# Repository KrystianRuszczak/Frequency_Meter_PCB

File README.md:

# STM32 Frequency Meter PCB

A four-layer KiCad board for measuring the frequency of periodic signals in the **50–100 MHz** range. A 50 Ω SMA input feeds an analog filter and amplifier. The STM32 counts pulses from that front end and is intended to show the result on a small OLED display.

| Design target | Value |
|---|---|
| Input frequency | 50–100 MHz |
| Minimum input amplitude | 10 mV peak (20 mV peak-to-peak for a sine wave) |
| Counter input after division | 25–50 MHz |
| Timebase | 16 MHz crystal |
| Power and data | 5 V from USB-C; USB 2.0 Full-Speed data lines routed to the STM32 |
| Display | 1.3-inch, 128 × 64 I²C OLED |

## Signal path

1. The signal enters through a 50 Ω edge-mount SMA connector and passes through a Butterworth LC band-pass filter designed for 50–100 MHz. A 49.9 Ω resistor terminates the filter output.
2. The LMH6629 amplifies the filtered signal. The REF2033 supplies a 1.65 V bias for the amplifier and comparison threshold.
3. The TLV3601 converts the amplified waveform into digital pulses. The SN74LVC1G80 divides the pulse rate by two before it reaches the STM32 on PA1.
4. The firmware is intended to count rising edges in a timed gate and calculate the input frequency as `f_in = 2 × counted_edges / gate_time`. With a 75 MHz input, the expected rate at PA1 is 37.5 MHz.

The board includes BOOT0 and RESET buttons, SWD access pads and test points for the comparator output, divided clock, reference and power rails.

## Key components

| Reference | Part | Role |
|---|---|---|
| IC1 | LMH6629MF/NOPB | RF amplifier |
| IC2 | SN74LVC1G80DBVR | Divide-by-two stage |
| IC3 | REF2033AIDDCT | 1.65 V bias output |
| IC4 | TLV3601DBVR | High-speed comparator |
| IC5 | USBLC6-4SC6 | USB data-line ESD protection |
| IC6 | STM32G431KBT6 | Timer-based pulse counting, USB and display control |
| U2 | AP2112K-3.3 | 3.3 V regulator |
| Y1 | ABM3B-16.000MHZ-10-1-U-T | External 16 MHz crystal |
| J1 | 50 Ω edge-mount SMA | RF input; PCB footprint based on Amphenol 132289 |
| J2 | USB4105-GF-A | USB-C power and data |
| DS1 | 1.3-inch, 128 × 64 I²C OLED | Display; header order: GND, 3.3 V, SCL, SDA |

The current PCB uses the **USBLC6-4SC6**. The board traces join pads 3 and 4 for D+ and pads 1 and 6 for D−; the four-channel protection device does not bridge those pairs internally.

## KiCad files

- [Project](pcb_design/Frequency_Meter.kicad_pro)
- [Schematic](pcb_design/Frequency_Meter.kicad_sch)
- [Four-layer PCB](pcb_design/Frequency_Meter.kicad_pcb)

Open the project in KiCad and use the schematic for passive component values and reference designators. Full library editing requires the local symbol and footprint libraries and their project library tables. Those files, along with the simulation workspaces and custom design rules, are excluded by the current `.gitignore`. If working from a clean clone, obtain the missing files separately and place the libraries where the tables expect them.

## Validation status

The schematic and four-layer layout are available. Transient simulations at **75 MHz and 10 mV peak** checked whether the front end still produced the expected pulse train in the presence of out-of-band interference. At **20 mV peak**, the tested interferers at **18, 21, 23 and 207 MHz** did not visibly add or remove pulses in the plotted windows. A stronger **207 MHz** interferer at **355 mV peak** produced extra transitions. These are simulation results for specific test cases, not a hardware interference limit.

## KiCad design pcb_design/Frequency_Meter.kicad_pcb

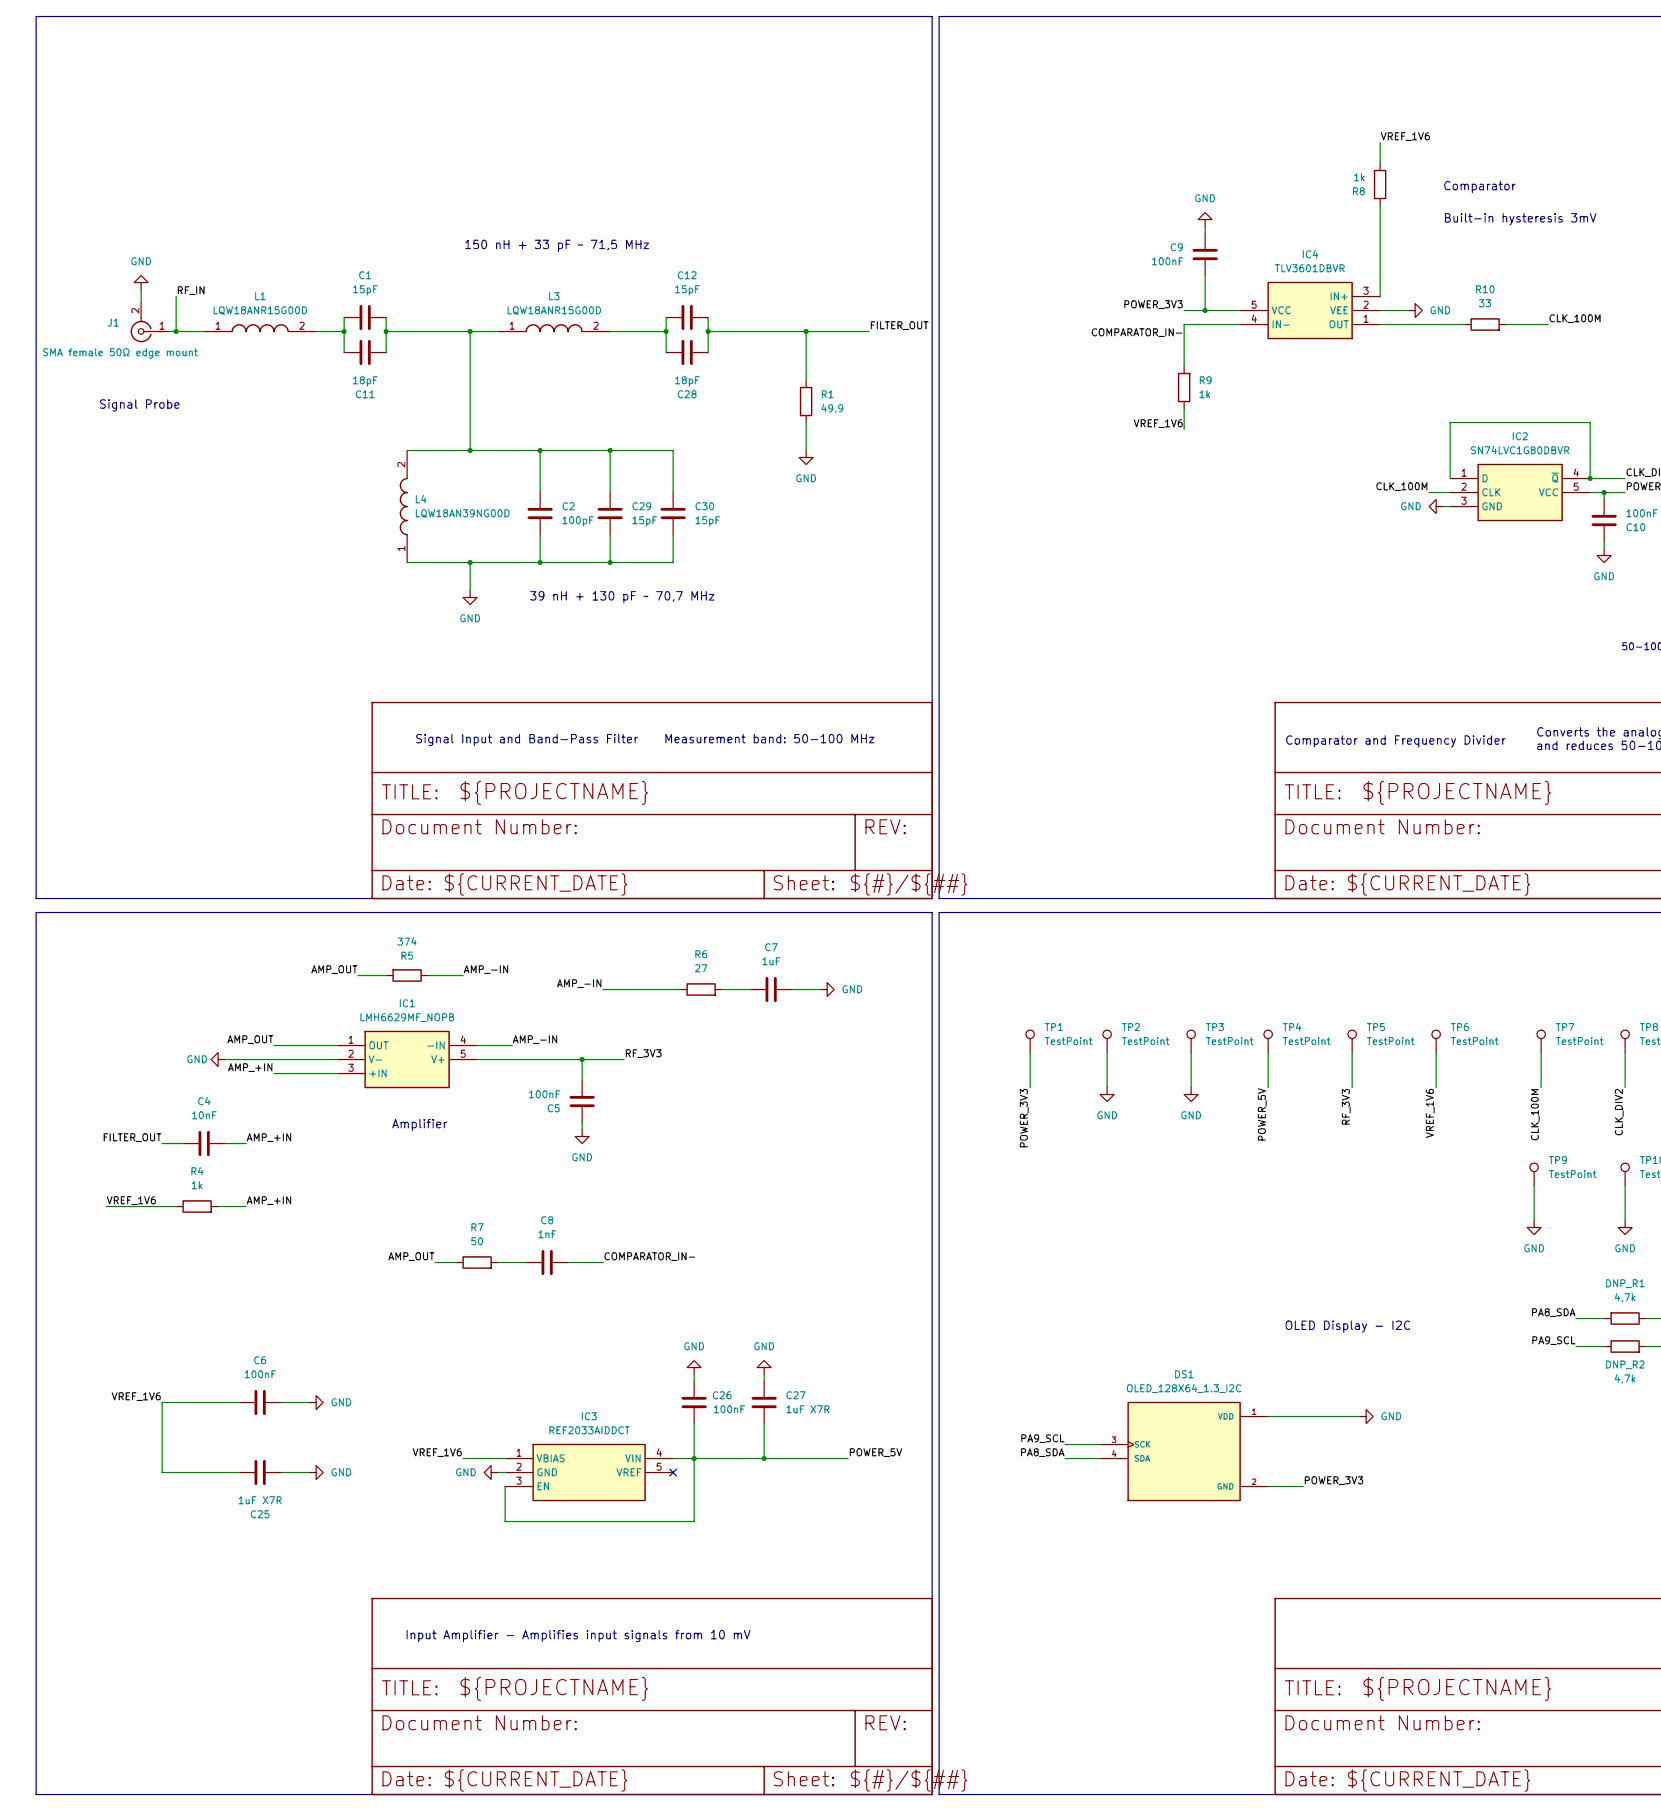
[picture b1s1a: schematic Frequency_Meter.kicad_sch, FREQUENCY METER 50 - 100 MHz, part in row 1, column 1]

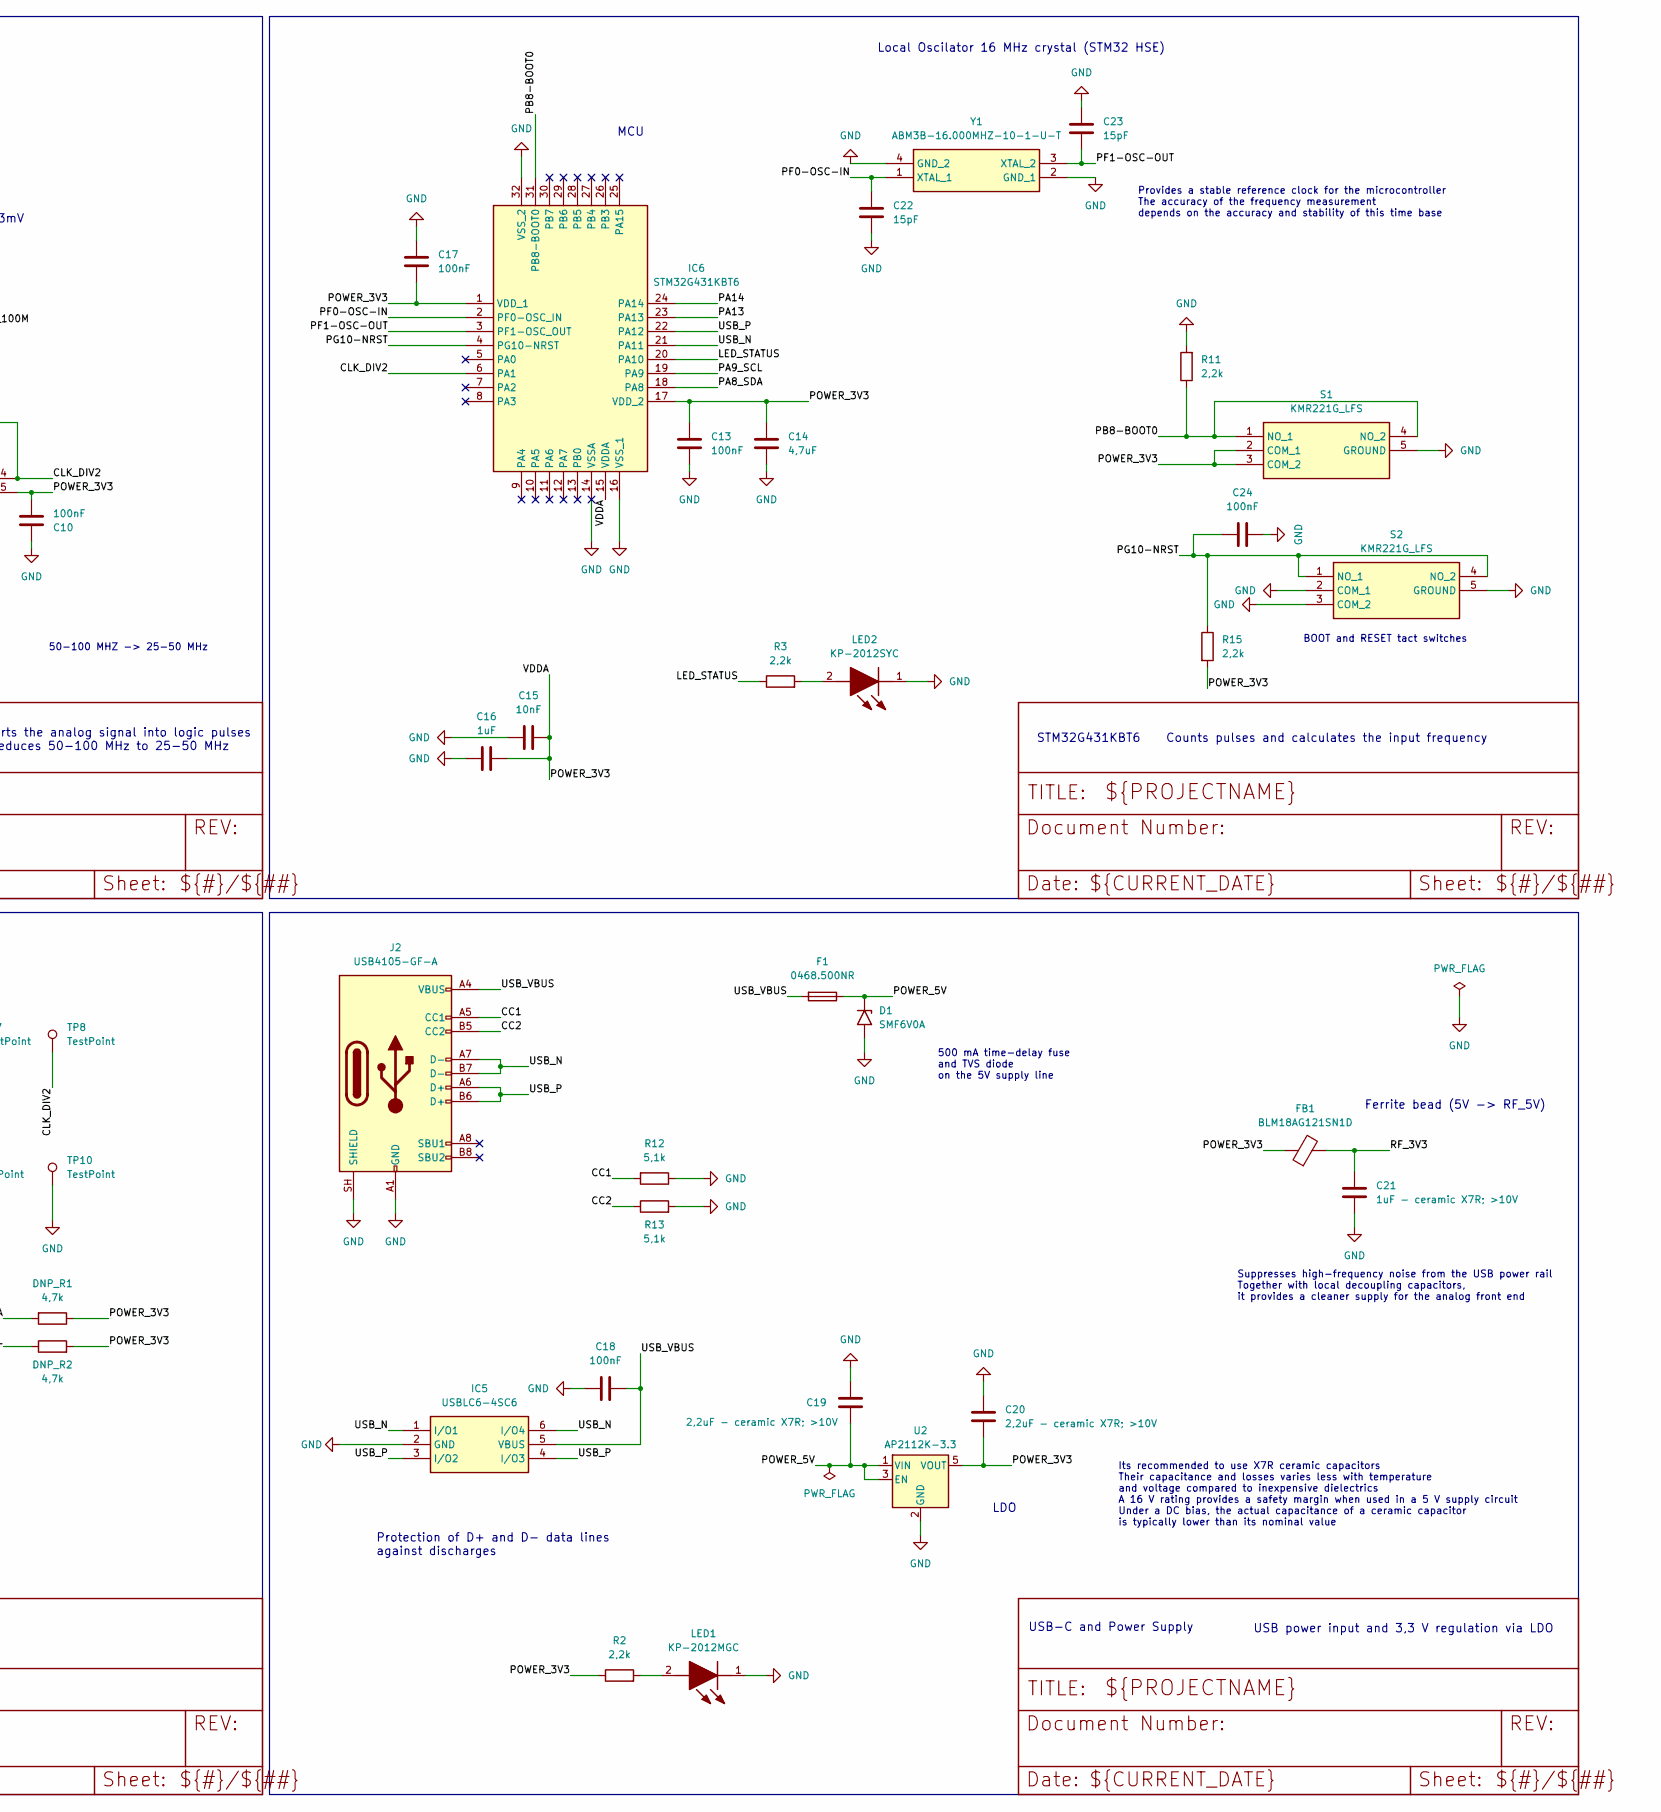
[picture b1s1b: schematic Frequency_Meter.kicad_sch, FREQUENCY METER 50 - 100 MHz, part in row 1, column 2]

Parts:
C1, C12, C22, C23, C29, C30: 15pF; C_0603_1608Metric_Pad1.08x0.95mm_HandSolder
C2: 100pF; C_0603_1608Metric_Pad1.08x0.95mm_HandSolder
C4, C15: 10nF; C_0805_2012Metric
C5, C6, C9, C10, C13, C17, C18, C24, C26: 100nF; C_0603_1608Metric_Pad1.08x0.95mm_HandSolder
C7, C16: 1uF; C_0805_2012Metric
C8: 1nF; C_0603_1608Metric_Pad1.08x0.95mm_HandSolder
C11, C28: 18pF; C_0603_1608Metric_Pad1.08x0.95mm_HandSolder
C14: 4,7uF; C_0805_2012Metric
C19, C20: 2,2uF - ceramic X7R; >10V; C_0805_2012Metric
C21: 1uF - ceramic X7R; >10V; C_0805_2012Metric
C25, C27: 1uF X7R; C_0805_2012Metric
D1: SMF6V0A; D_SMF
DNP_R1, DNP_R2: 4,7k; R_0603_1608Metric_Pad0.98x0.95mm_HandSolder
DS1: OLED_128X64_1.3_I2C; LCD_OLED_128X64_1.3_I2C; PARTREV NA
F1: 0468.500NR; Fuse_1206_3216Metric
FB1: BLM18AG121SN1D; L_0603_1608Metric_Pad1.05x0.95mm_HandSolder
IC1: LMH6629MF_NOPB; SOT95P280X145-5N; Mouser Part Number 926-LMH6629MF/NOPB
IC2: SN74LVC1G80DBVR; SOT95P280X145-5N; Mouser Part Number 595-SN74LVC1G80DBVR
IC3: REF2033AIDDCT; SOT95P280X110-5N; Mouser Part Number 595-REF2033AIDDCT
IC4: TLV3601DBVR; SOT95P280X145-5N; Mouser Part Number 595-TLV3601DBVR
IC5: USBLC6-4SC6; SOT95P280X145-6N; Manufacturer_Part_Number USBLC6-4SC6
IC6: STM32G431KBT6; QFP80P900X900X160-32N; Manufacturer_Part_Number STM32G431KBT6
J1: SMA female 50Ω edge mount; SMA_Amphenol_132289_EdgeMount
J2: USB4105-GF-A; USB_C_Receptacle_GCT_USB4105-xx-A_16P_TopMnt_Horizontal
L1, L3: LQW18ANR15G00D; L_0603_1608Metric_Pad1.05x0.95mm_HandSolder; Manufacturer_Part_Number LQW18ANR15G00D
L4: LQW18AN39NG00D; L_0603_1608Metric_Pad1.05x0.95mm_HandSolder; Manufacturer_Part_Number LQW18AN39NG00D
LED1: KP-2012MGC; LEDC2012X110N; Manufacturer_Part_Number KP-2012MGC
LED2: KP-2012SYC; LEDC2012X110N; Manufacturer_Part_Number KP-2012SYC
R1: 49,9; R_0603_1608Metric_Pad0.98x0.95mm_HandSolder
R2, R3, R11, R15: 2,2k; R_0603_1608Metric_Pad0.98x0.95mm_HandSolder
R4, R8, R9: 1k; R_0603_1608Metric_Pad0.98x0.95mm_HandSolder
R5: 374; R_0603_1608Metric_Pad0.98x0.95mm_HandSolder
R6: 27; R_0603_1608Metric_Pad0.98x0.95mm_HandSolder
R7: 50; R_0603_1608Metric_Pad0.98x0.95mm_HandSolder
R10: 33; R_0603_1608Metric_Pad0.98x0.95mm_HandSolder
R12, R13: 5,1k; R_0603_1608Metric_Pad0.98x0.95mm_HandSolder
S1, S2: KMR221G_LFS; KMR221GLFS; Manufacturer_Part_Number KMR221G LFS
TP1, TP4, TP5, TP6, TP7, TP8: TestPoint; TestPoint_Pad_D1.0mm
TP2, TP3, TP9, TP10: TestPoint; TestPoint_THTPad_D1.0mm_Drill0.5mm
U2: AP2112K-3.3; SOT-23-5
Y1: ABM3B-16.000MHZ-10-1-U-T; ABM3B; Manufacturer_Part_Number ABM3B-16.000MHZ-10-1-U-T

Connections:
/AMP_+IN: C4.2, IC1.3 (+IN), R4.2
/AMP_-IN: IC1.4 (-IN), R5.1, R6.1
/AMP_OUT: IC1.1 (OUT), R5.2, R7.1
/CC1: J2.A5 (CC1), R12.2
/CC2: J2.B5 (CC2), R13.1
/CLK_100M: IC2.2 (CLK), R10.2, TP7.1 (1_1)
/CLK_DIV2: IC2.1 (D), IC2.4 (~Q), IC6.6 (PA1), TP8.1 (1_1)
/COMPARATOR_IN-: C8.1, IC4.4 (IN-), R9.2
/FILTER_OUT: C4.1, C12.2, C28.2, R1.1
/LED_STATUS: IC6.20 (PA10), R3.1
/PA8_SDA: DNP_R1.2, DS1.4 (SDA), IC6.18 (PA8)
/PA9_SCL: DNP_R2.1, DS1.3 (SCK), IC6.19 (PA9)
/PA13: IC6.23 (PA13)
/PA14: IC6.24 (PA14)
/PB8-BOOT0: IC6.31 (PB8-BOOT0), R11.1, S1.1 (NO_1), S1.4 (NO_2)
/PF0-OSC-IN: C22.1, IC6.2 (PF0-OSC_IN), Y1.1 (XTAL_1)
/PF1-OSC-OUT: C23.2, IC6.3 (PF1-OSC_OUT), Y1.3 (XTAL_2)
/PG10-NRST: C24.1, IC6.4 (PG10-NRST), R15.1, S2.1 (NO_1), S2.4 (NO_2)
/POWER_3V3: C9.1, C10.2, C13.1, C14.1, C15.2, C16.2, C17.1, C20.2, DNP_R1.1, DNP_R2.2, DS1.2 (GND), FB1.1, IC2.5 (VCC), IC4.5 (VCC), IC6.1 (VDD_1), IC6.15 (VDDA), IC6.17 (VDD_2), R2.1, R15.2, S1.2 (COM_1), S1.3 (COM_2), TP1.1 (1_1), U2.5 (VOUT)
/POWER_5V: C19.2, C26.1, C27.2, D1.1 (A1), F1.1, IC3.3 (EN), IC3.4 (VIN), TP4.1 (1_1), U2.1 (VIN), U2.3 (EN)
/RF_3V3: C5.2, C21.1, FB1.2, IC1.5 (V+), TP5.1 (1_1)
/RF_IN: J1.1 (In), L1.1
/USB_N: IC5.1 (I/O1), IC5.6 (I/O4), IC6.21 (PA11), J2.A7 (D-), J2.B7 (D-)
/USB_P: IC5.3 (I/O2), IC5.4 (I/O3), IC6.22 (PA12), J2.A6 (D+), J2.B6 (D+)
/USB_VBUS: C18.2, F1.2, IC5.5 (VBUS), J2.A4 (VBUS), J2.A9 (VBUS), J2.B4 (VBUS), J2.B9 (VBUS)
/VREF_1V6: C6.1, C25.1, IC3.1 (VBIAS), R4.1, R8.1, R9.1, TP6.1 (1_1)
GND: C2.2, C5.1, C6.2, C7.2, C9.2, C10.1, C13.2, C14.2, C15.1, C16.1, C17.2, C18.1, C19.1, C20.1, C21.2, C22.2, C23.1, C24.2, C25.2, C26.2, C27.1, C29.1, C30.1, D1.2 (A2), DS1.1 (VDD), IC1.2 (V-), IC2.3 (GND), IC3.2 (GND), IC4.2 (VEE), IC5.2 (GND), IC6.14 (VSSA), IC6.16 (VSS_1), IC6.32 (VSS_2), J1.2 (Ext), J2.A1 (GND), J2.A12 (GND), J2.B1 (GND), J2.B12 (GND), J2.SH (SHIELD), L4.1, LED1.1 (K), LED2.1 (K), R1.2, R11.2, R12.1, R13.2, S1.5 (GROUND), S2.2 (COM_1), S2.3 (COM_2), S2.5 (GROUND), TP2.1 (1_1), TP3.1 (1_1), TP9.1 (1_1), TP10.1 (1_1), U2.2 (GND), Y1.2 (GND_1), Y1.4 (GND_2)
unnamed: C1.1, C11.1, L1.2
unnamed: C1.2, C2.1, C11.2, C29.2, C30.2, L3.1, L4.2
unnamed: C7.1, R6.2
unnamed: C8.2, R7.2
unnamed: C12.1, C28.1, L3.2
unnamed: IC4.3 (IN+), R8.2
unnamed: IC4.1 (OUT), R10.1
unnamed: LED1.2 (A), R2.2
unnamed: LED2.2 (A), R3.2

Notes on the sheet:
Input Amplifier - Amplifies input signals from 10 mV
STM32G431KBT6 Counts pulses and calculates the input frequency
Provides a stable reference clock for the microcontroller The accuracy of the frequency measurement depends on the accuracy and stability of this time base
MCU
BOOT and RESET tact switches
Converts the analog signal into logic pulses and reduces 50-100 MHz to 25-50 MHz
LDO
Protection of D+ and D− data lines against discharges
150 nH + 33 pF ~ 71,5 MHz
Its recommended to use X7R ceramic capacitors Their capacitance and losses varies less with temperature and voltage compared to inexpensive dielectrics A 16 V rating provides a safety margin when used in a 5 V supply circuit Under a DC bias, the actual capacitance of a ceramic capacitor is typicall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
Comparator and Frequency Divider
500 mA time-delay fuse and TVS diode on the 5V supply line
Amplifier
Signal Input and Band-Pass Filter Measurement band: 50-100 MHz
50-100 MHZ -> 25-50 MHz
USB-C and Power Supply
Signal Probe
Suppresses high-frequency noise from the USB power rail Together with local decoupling capacitors, it provides a cleaner supply for the analog front end
Comparator
39 nH + 130 pF ~ 70,7 MHz
Ferrite bead (5V -> RF_5V)
Built-in hysteresis 3mV
OLED Display - I2C
USB power input and 3,3 V regulation via LDO
Local Oscilator 16 MHz crystal (STM32 HSE)

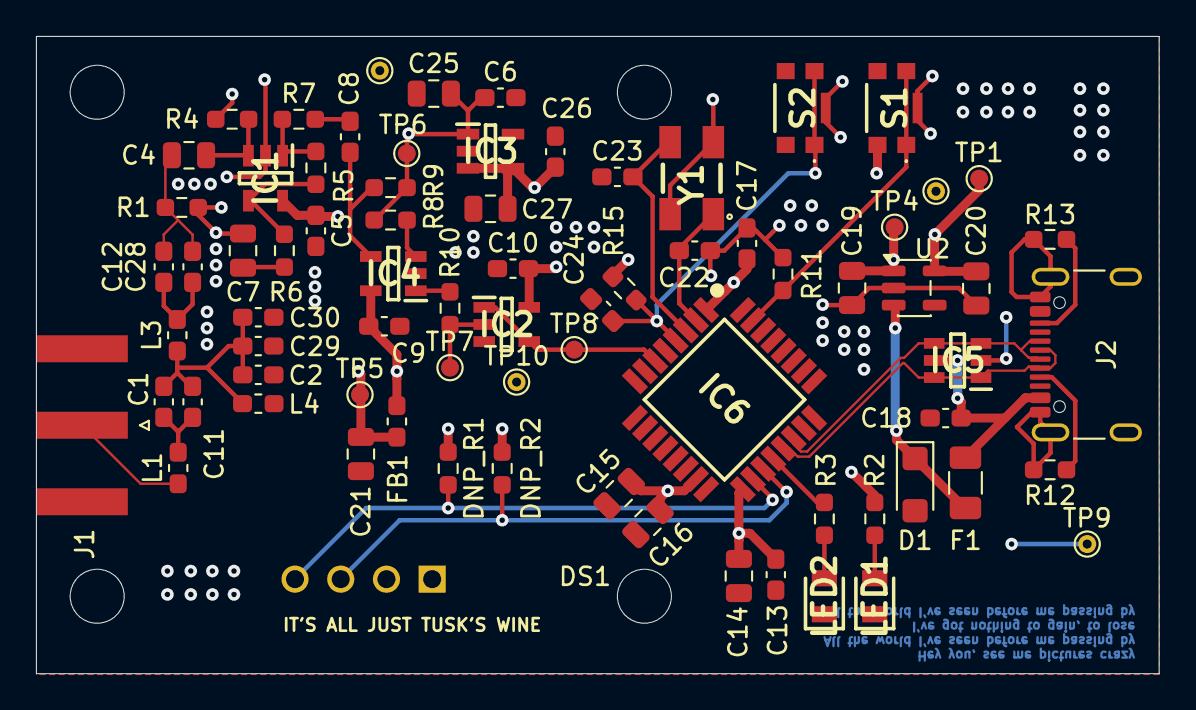
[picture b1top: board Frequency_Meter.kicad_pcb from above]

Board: 4 copper layers, 62.4 x 35.4 mm, 76 parts (0 on the bottom side), 34 nets.
